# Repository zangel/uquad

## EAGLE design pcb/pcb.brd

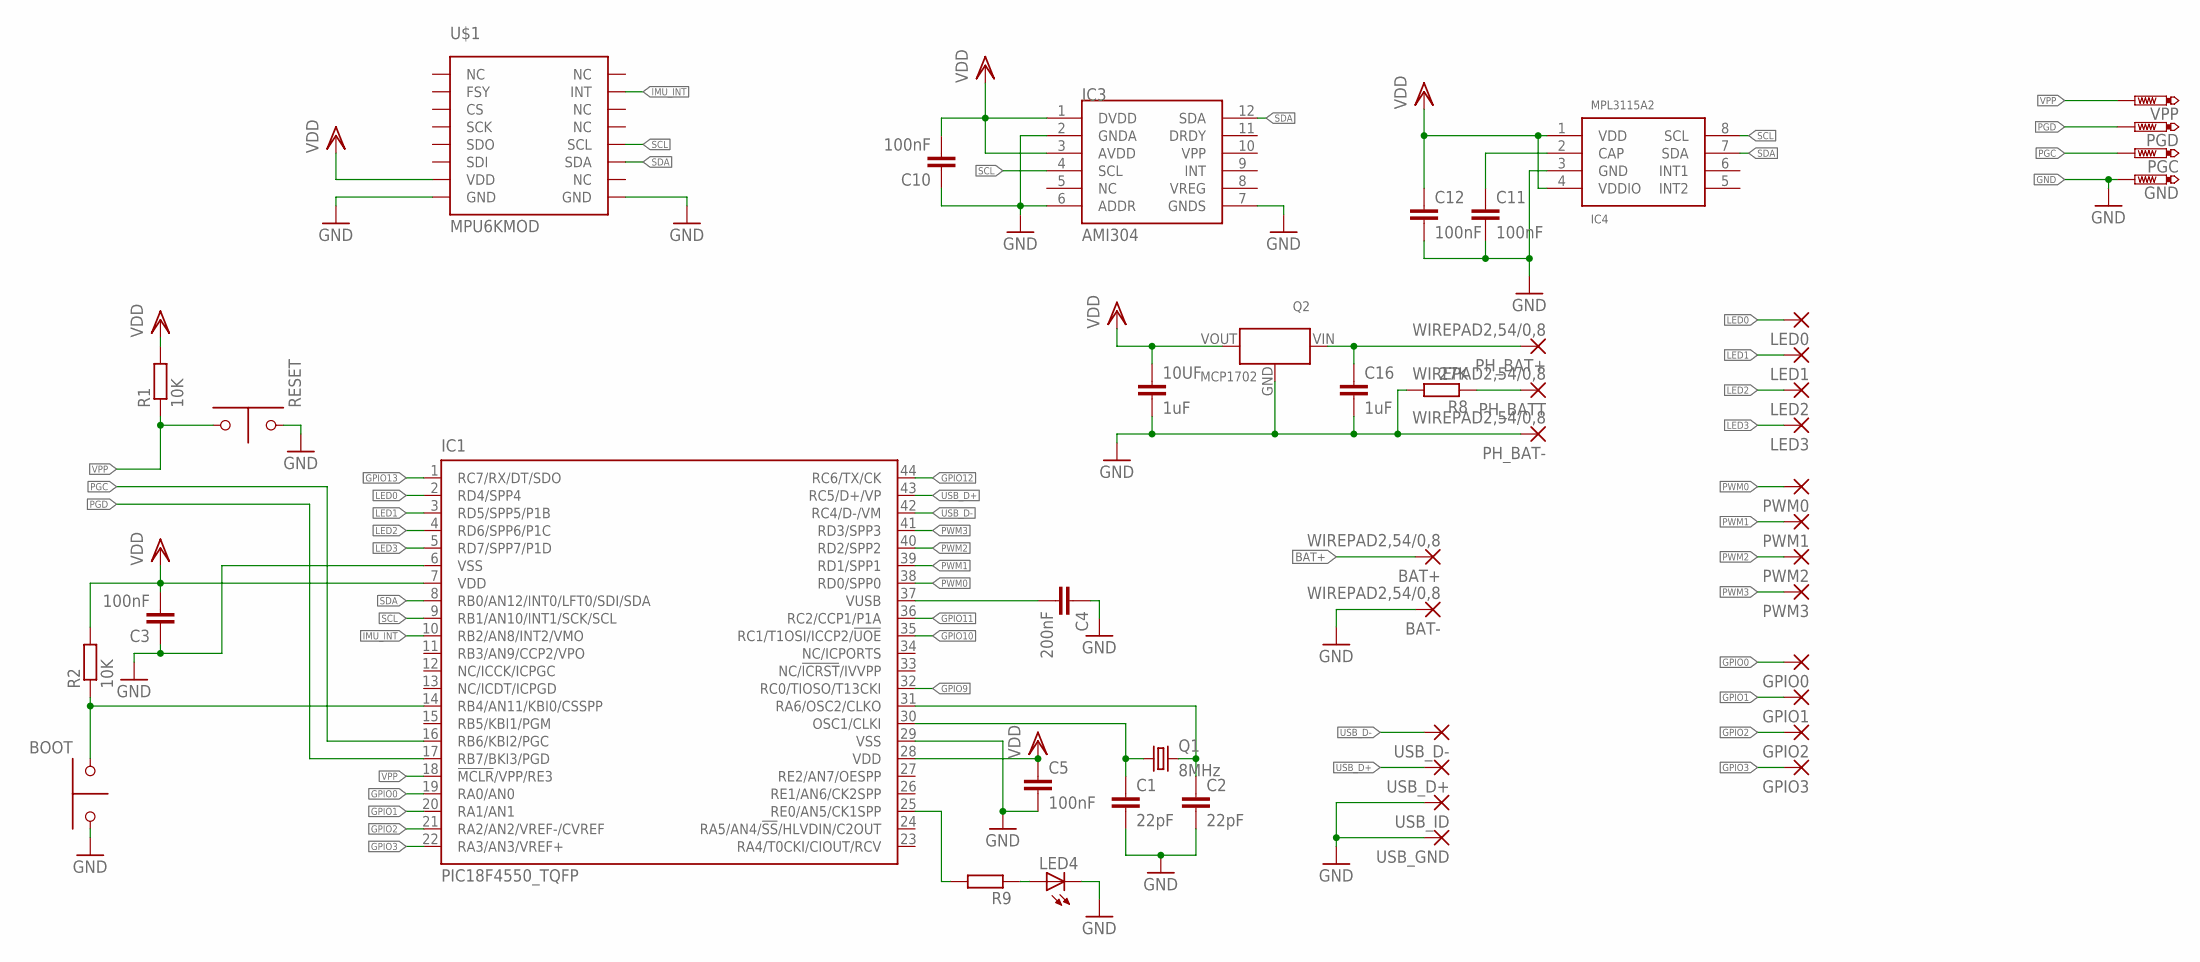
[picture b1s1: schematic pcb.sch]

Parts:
10UF: 1uF; C1206K
BAT+: WIREPAD2,54/0,8; 2,54/0,8
BAT-: WIREPAD2,54/0,8; 2,54/0,8
BOOT: SW2
C1, C2: 22pF; C1206
C3, C5, C10, C11, C12: 100nF; C1206
C4: 200nF; C1206
C16: 1uF; C1206K
GND: PTR1TP12SQ; TP12SQ
GPIO0, GPIO1, GPIO2, GPIO3: SMD2; SMD1,27-2,54
IC1: PIC18F4550_TQFP; TQFP44
IC3: AMI304; LGA12
IC4: MPL3115A2; LGA8
LED0, LED1, LED2, LED3: SMD2; SMD1,27-2,54
LED4: LEDKA-3528ASYC; KA-3528ASYC
PGC: PTR1TP12SQ; TP12SQ
PGD: PTR1TP12SQ; TP12SQ
PH_BAT+: WIREPAD2,54/0,8; 2,54/0,8
PH_BAT-: WIREPAD2,54/0,8; 2,54/0,8
PH_BATT: WIREPAD2,54/0,8; 2,54/0,8
PWM0, PWM1, PWM2, PWM3: SMD2; SMD1,27-2,54
Q1: 8MHz; HC49/S
Q2: MCP1702; TO-92
R1, R2: 10K; R1206
R8: 27K; R1206
R9: R-EU_R1206; R1206
RESET: SW2
U$1: MPU6KMOD
USB_D+: SMD2; SMD1,27-2,54
USB_D-: SMD2; SMD1,27-2,54
USB_GND: SMD2; SMD1,27-2,54
USB_ID: SMD2; SMD1,27-2,54
VPP: PTR1TP12SQ; TP12SQ

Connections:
BAT+: BAT+.1, C16.1, PH_BAT+.1, Q2.VIN
BATT: PH_BATT.1, R8.1
GND: 10UF.2, BAT-.1, BOOT.1, C1.2, C2.2, C3.1, C4.1, C5.2, C10.1, C11.2, C12.2, C16.2, GND.TP, IC1.6 (VSS), IC1.29 (VSS), IC3.2 (GNDA), IC3.6 (ADDR), IC3.7 (GNDS), IC4.3 (GND), LED4.C, PH_BAT-.1, Q2.GND, R8.2, RESET.2, U$1.P$8 (GND), U$1.P$16 (GND), USB_GND.1, USB_ID.1
GPIO0: GPIO0.1, IC1.19 (RA0/AN0)
GPIO1: GPIO1.1, IC1.20 (RA1/AN1)
GPIO2: GPIO2.1, IC1.21 (RA2/AN2/VREF-/CVREF)
GPIO3: GPIO3.1, IC1.22 (RA3/AN3/VREF+)
GPIO9: IC1.32 (RC0/TIOSO/T13CKI)
GPIO10: IC1.35 (RC1/T1OSI/ICCP2/!UOE)
GPIO11: IC1.36 (RC2/CCP1/P1A)
GPIO12: IC1.44 (RC6/TX/CK)
GPIO13: IC1.1 (RC7/RX/DT/SDO)
IMU_INT: IC1.10 (RB2/AN8/INT2/VMO), U$1.P$10 (INT)
LED0: IC1.2 (RD4/SPP4), LED0.1
LED1: IC1.3 (RD5/SPP5/P1B), LED1.1
LED2: IC1.4 (RD6/SPP6/P1C), LED2.1
LED3: IC1.5 (RD7/SPP7/P1D), LED3.1
unnamed: C1.1, IC1.30 (OSC1/CLKI), Q1.1
unnamed: C4.2, IC1.37 (VUSB)
unnamed: C2.1, IC1.31 (RA6/OSC2/CLKO), Q1.2
unnamed: BOOT.2, IC1.14 (RB4/AN11/KBI0/CSSPP), R2.1
unnamed: C11.1, IC4.2 (CAP)
unnamed: IC1.25 (RE0/AN5/CK1SPP), R9.2
unnamed: LED4.A, R9.1
PGC: IC1.16 (RB6/KBI2/PGC), PGC.TP
PGD: IC1.17 (RB7/BKI3/PGD), PGD.TP
PWM0: IC1.38 (RD0/SPP0), PWM0.1
PWM1: IC1.39 (RD1/SPP1), PWM1.1
PWM2: IC1.40 (RD2/SPP2), PWM2.1
PWM3: IC1.41 (RD3/SPP3), PWM3.1
SCL: IC1.9 (RB1/AN10/INT1/SCK/SCL), IC3.4 (SCL), IC4.8 (SCL), U$1.P$13 (SCL)
SDA: IC1.8 (RB0/AN12/INT0/LFT0/SDI/SDA), IC3.12 (SDA), IC4.7 (SDA), U$1.P$14 (SDA)
USB_D+: IC1.43 (RC5/D+/VP), USB_D+.1
USB_D-: IC1.42 (RC4/D-/VM), USB_D-.1
VDD: 10UF.1, C3.2, C5.1, C10.2, C12.1, IC1.7 (VDD), IC1.28 (VDD), IC3.1 (DVDD), IC3.3 (AVDD), IC4.1 (VDD), IC4.4 (VDDIO), Q2.VOUT, R1.2, R2.2, U$1.P$7 (VDD)
VPP: IC1.18 (!MCLR!/VPP/RE3), R1.1, RESET.1, VPP.TP

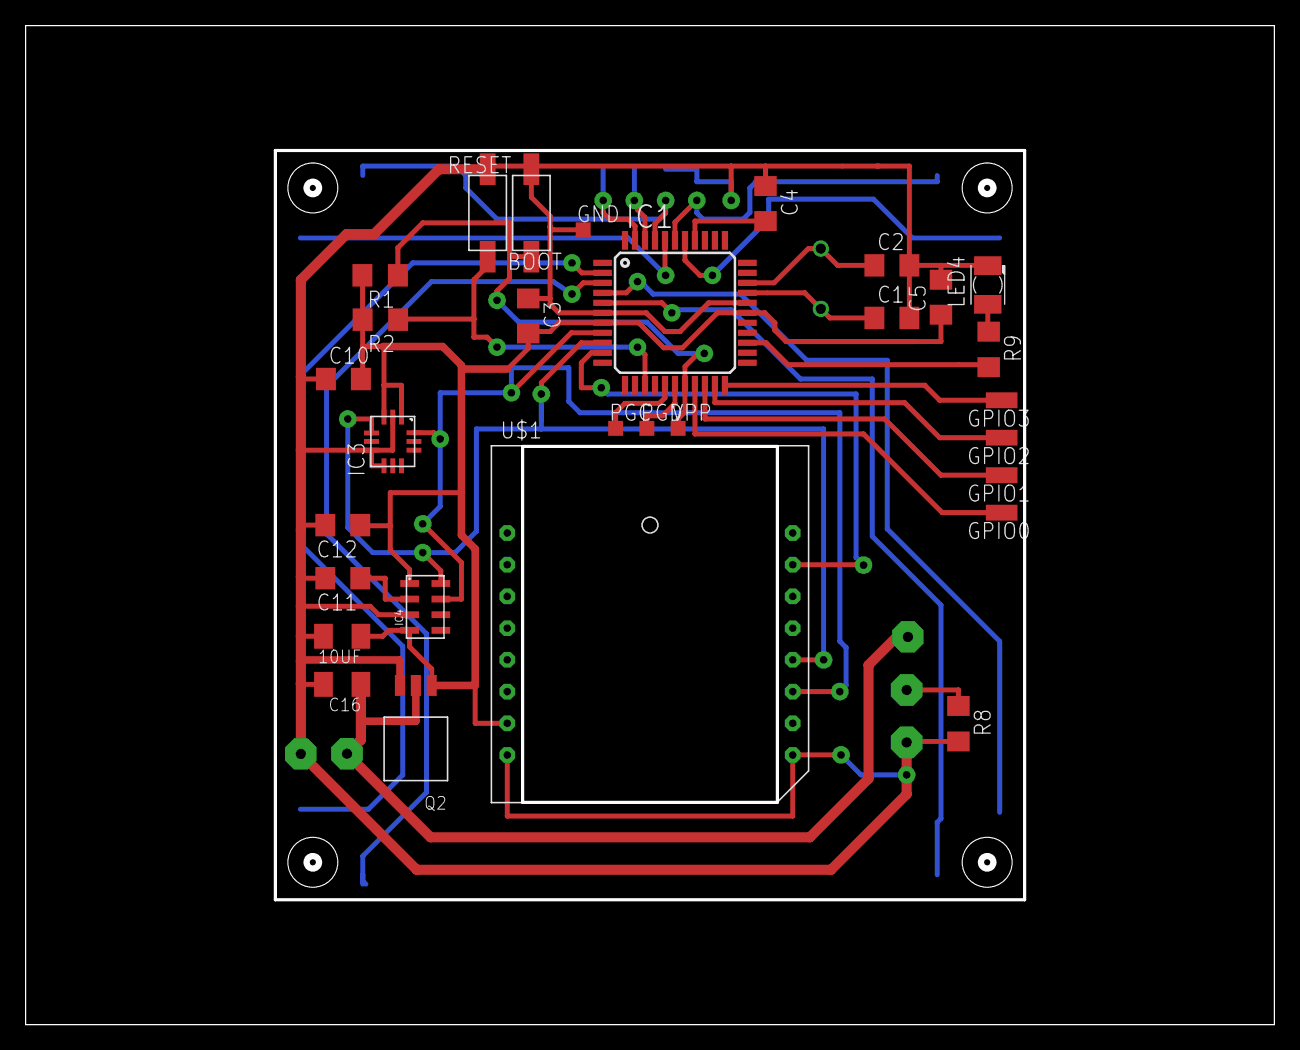
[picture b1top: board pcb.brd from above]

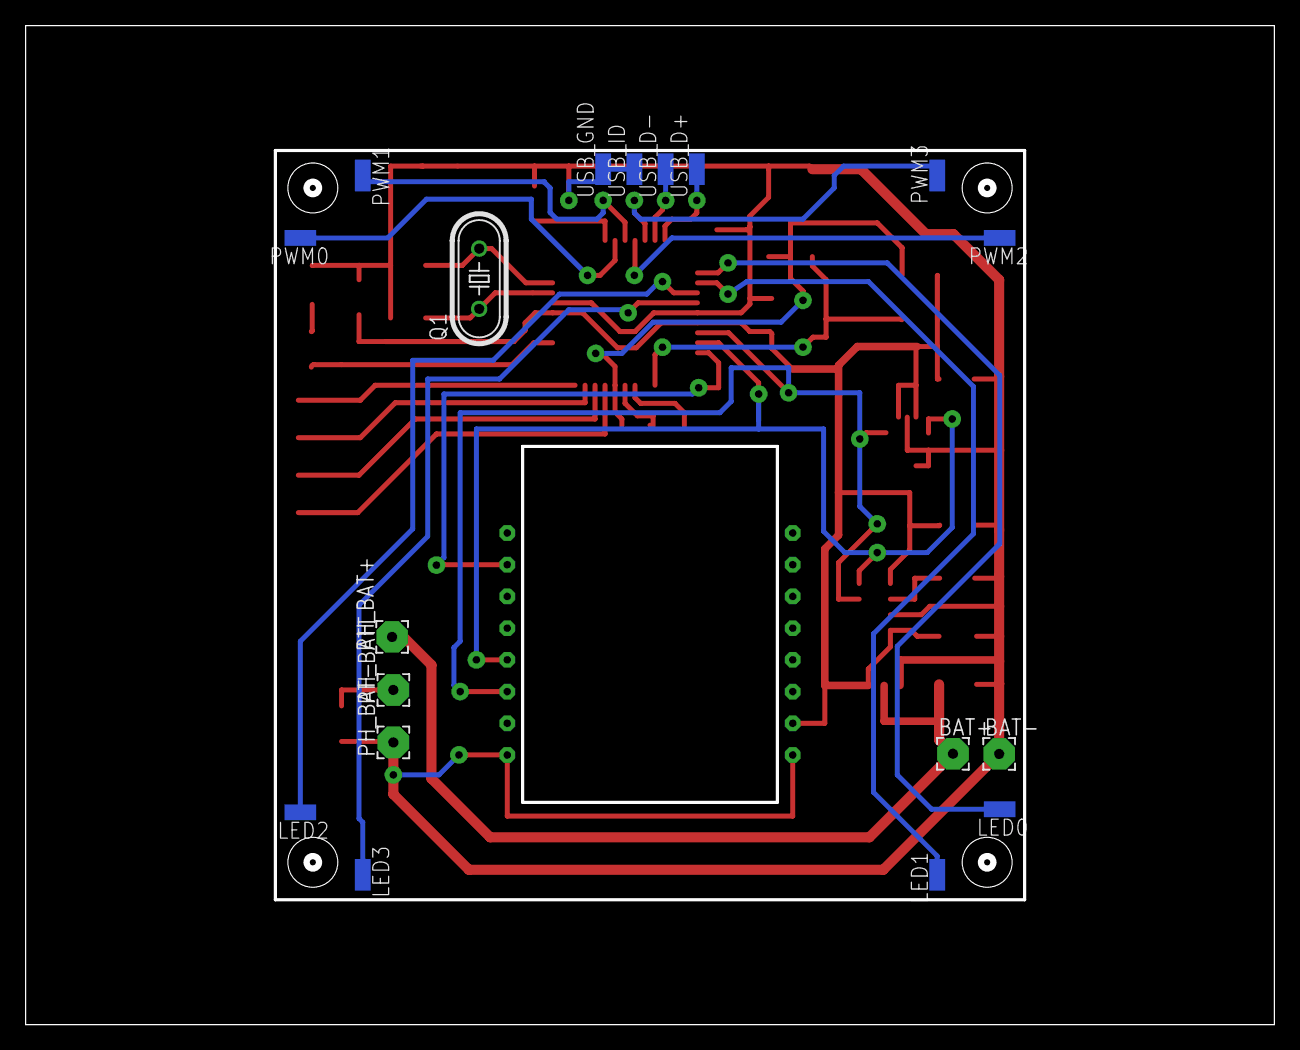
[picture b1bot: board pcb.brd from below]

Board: 2 copper layers, 100.0 x 80.0 mm, 48 parts (18 on the bottom side), 31 nets.

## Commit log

2016-02-17 added pcb
2016-03-14 - accelerometer calibration related code; - removed unused code;
2016-04-21 - applied arm64 bit clang fixes to Eigen; - small refactoring in Qt PoseEstimation app; - added new blocks to squad::control; - replaced iSensorFS and iOversampleRatio with fSensorDT;
2016-06-02 - refactoring uquad::control
